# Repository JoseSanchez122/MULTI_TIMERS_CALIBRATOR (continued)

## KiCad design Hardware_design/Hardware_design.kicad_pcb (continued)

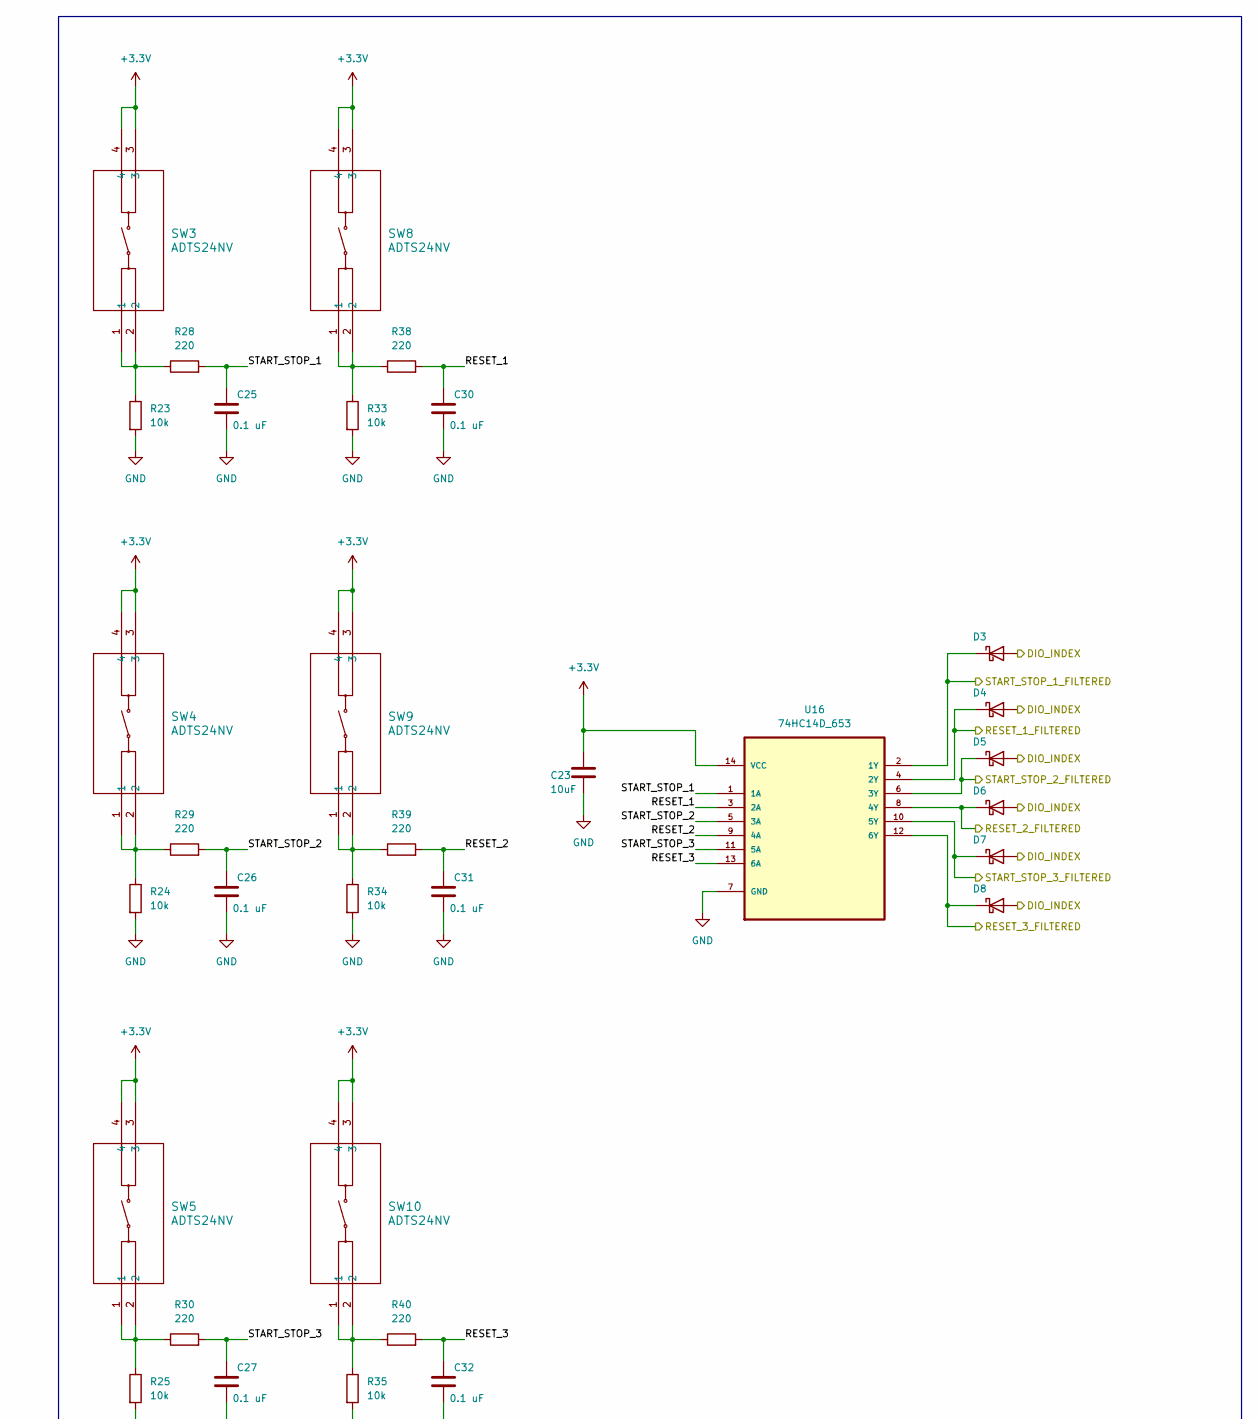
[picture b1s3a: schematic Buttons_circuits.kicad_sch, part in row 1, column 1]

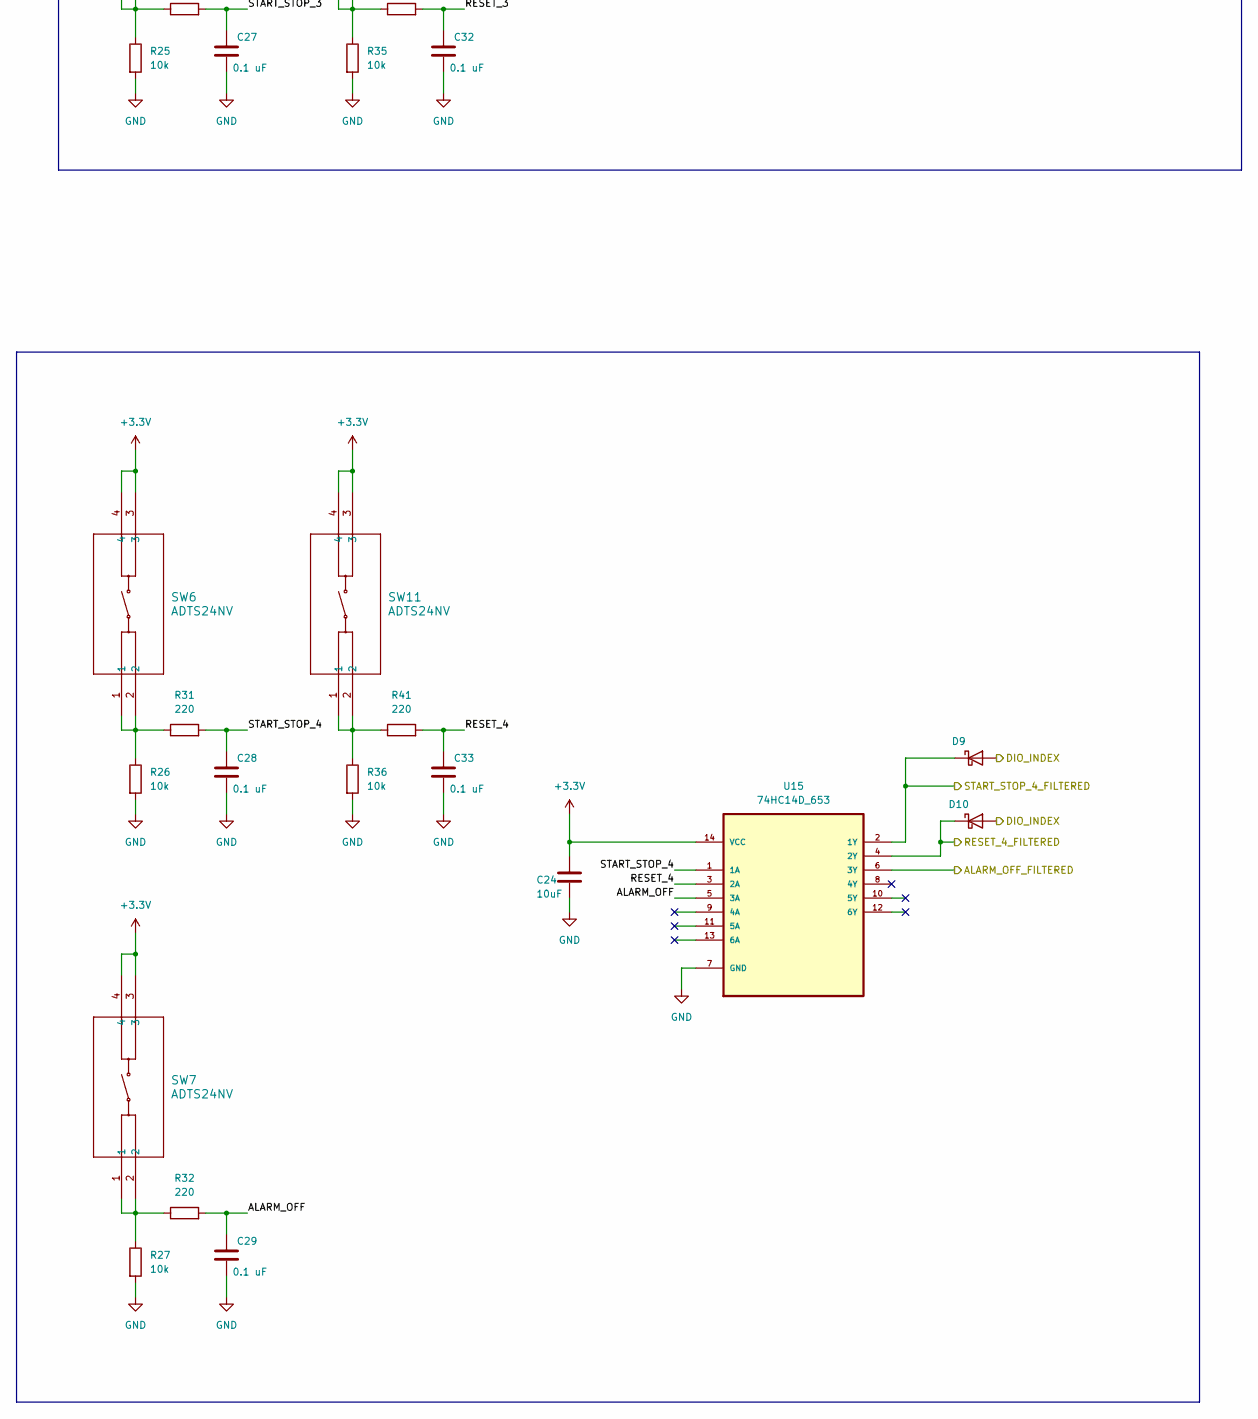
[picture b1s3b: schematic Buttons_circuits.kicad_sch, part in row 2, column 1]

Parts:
C23, C24: 10uF; 0805_SMD_TANT_CAP_T491B106K016AT
C25, C26, C27, C28, C29, C30, C31, C32, C33: 0.1 uF; 0805_SMD_CERAMIC_CAP_T491B106K016AT
D3, D4, D5, D6, D7, D8, D9, D10: D_Schottky; DIO_Schottky _MBR0530T3G
R23, R24, R25, R26, R27, R33, R34, R35, R36: 10k; 0805_RES_RESC2012X60N
R28, R29, R30, R31, R32, R38, R39, R40, R41: 220; 0805_RES_RESC2012X60N
SW3, SW4, SW5, SW6, SW7, SW8, SW9, SW10, SW11: ADTS24NV; PUSH_BUTTON_ADTS24NV
U15, U16: 74HC14D_653; Schimitt_Trigger_74HC14D_653; MPN 74HCT14D,653

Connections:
+3.3V: C23.1, C24.1, SW3.3, SW3.4, SW4.3, SW4.4, SW5.3, SW5.4, SW6.3, SW6.4, SW7.3, SW7.4, SW8.3, SW8.4, SW9.3, SW9.4, SW10.3, SW10.4, SW11.3, SW11.4, U15.14 (VCC), U16.14 (VCC); also elsewhere on the board
/Alarm_OFF_FILTERED: U15.6 (3Y); also elsewhere on the board
/Buttons_circuits/ALARM_OFF: C29.1, R32.2, U15.5 (3A)
/Buttons_circuits/RESET_1: C30.1, R38.2, U16.3 (2A)
/Buttons_circuits/RESET_2: C31.1, R39.2, U16.9 (4A)
/Buttons_circuits/RESET_3: C32.1, R40.2, U16.13 (6A)
/Buttons_circuits/RESET_4: C33.1, R41.2, U15.3 (2A)
/Buttons_circuits/START_STOP_1: C25.1, R28.2, U16.1 (1A)
/Buttons_circuits/START_STOP_2: C26.1, R29.2, U16.5 (3A)
/Buttons_circuits/START_STOP_3: C27.1, R30.2, U16.11 (5A)
/Buttons_circuits/START_STOP_4: C28.1, R31.2, U15.1 (1A)
/INDEX: D3.A, D4.A, D5.A, D6.A, D7.A, D8.A, D9.A, D10.A; also elsewhere on the board
/RESET_1_FILTERED: D4.C (K), U16.4 (2Y); also elsewhere on the board
/RESET_2_FILTERED: D6.C (K), U16.8 (4Y); also elsewhere on the board
/RESET_3_FILTERED: D8.C (K), U16.12 (6Y); also elsewhere on the board
/RESET_4_FILTERED: D10.C (K), U15.4 (2Y); also elsewhere on the board
/START_STOP_1_FILTERED: D3.C (K), U16.2 (1Y); also elsewhere on the board
/START_STOP_2_FILTERED: D5.C (K), U16.6 (3Y); also elsewhere on the board
/START_STOP_3_FILTERED: D7.C (K), U16.10 (5Y); also elsewhere on the board
/START_STOP_4_FILTERED: D9.C (K), U15.2 (1Y); also elsewhere on the board
GND: C23.2, C24.2, C25.2, C26.2, C27.2, C28.2, C29.2, C30.2, C31.2, C32.2, C33.2, R23.2, R24.2, R25.2, R26.2, R27.2, R33.2, R34.2, R35.2, R36.2, U15.7 (GND), U16.7 (GND); also elsewhere on the board
unnamed: R23.1, R28.1, SW3.1, SW3.2
unnamed: R24.1, R29.1, SW4.1, SW4.2
unnamed: R25.1, R30.1, SW5.1, SW5.2
unnamed: R26.1, R31.1, SW6.1, SW6.2
unnamed: R27.1, R32.1, SW7.1, SW7.2
unnamed: R33.1, R38.1, SW8.1, SW8.2
unnamed: R34.1, R39.1, SW9.1, SW9.2
unnamed: R35.1, R40.1, SW10.1, SW10.2
unnamed: R36.1, R41.1, SW11.1, SW11.2

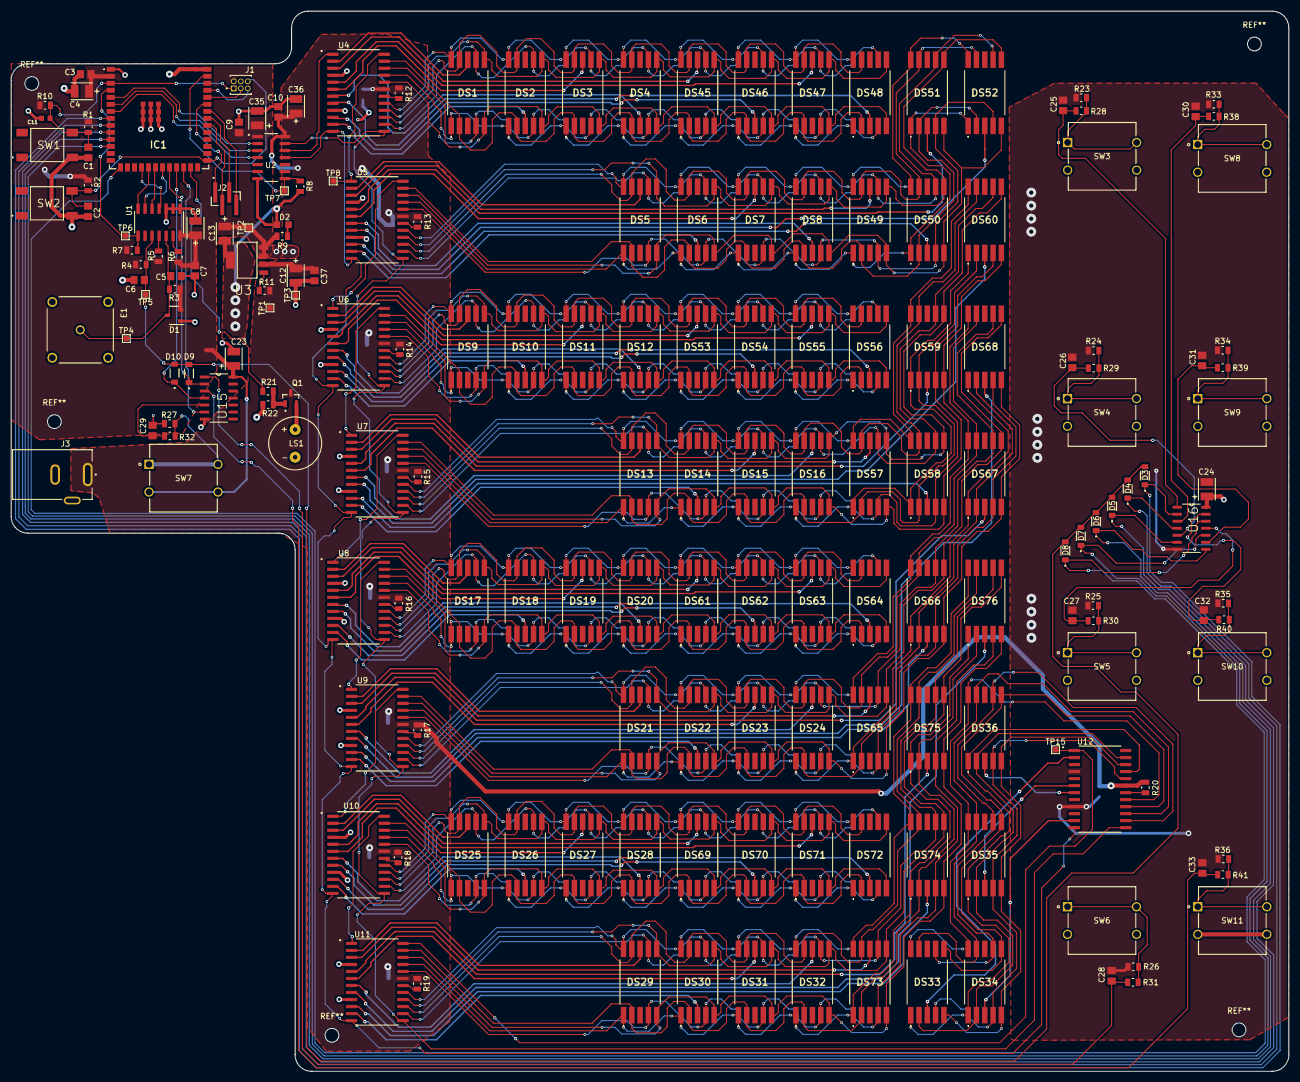
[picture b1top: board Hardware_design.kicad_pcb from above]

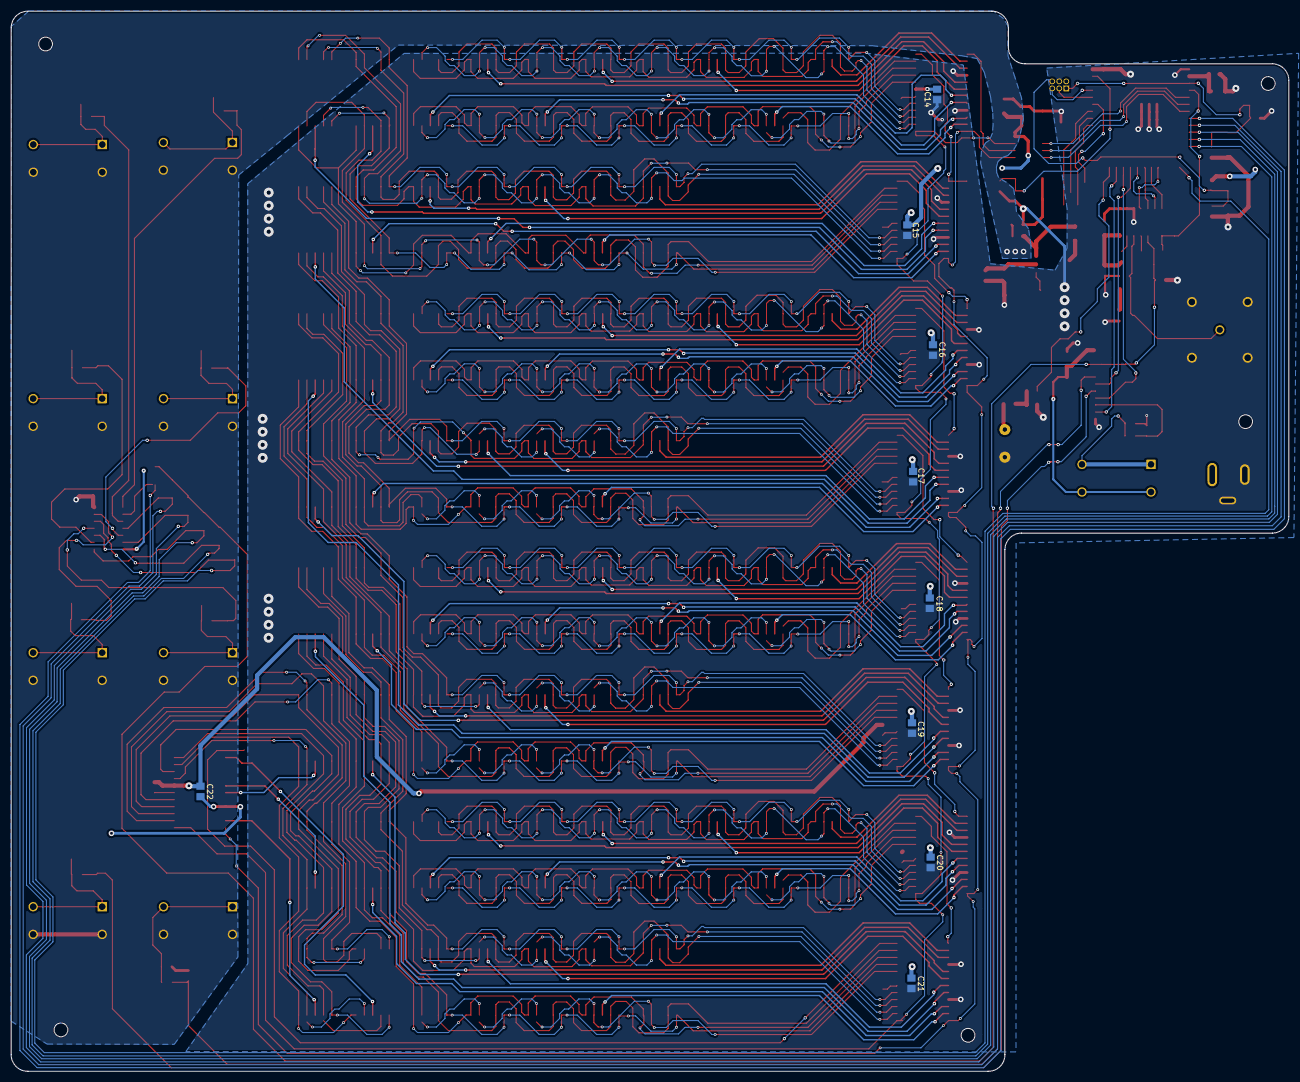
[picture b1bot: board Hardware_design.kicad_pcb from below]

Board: 2 copper layers, 231.3 x 191.9 mm, 195 parts (9 on the bottom side), 216 nets.

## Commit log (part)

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2026-05-24 primeros archivos
    primeros archivos
2026-05-24 sub folder created for examples
2026-05-25 starting the spi comunication example
2026-05-25 starting spi driver configuration
2026-05-29 hardware design initiated
2026-05-29 SPI_comnunication done, starting main firmware
2026-05-29 Update main.c
    seting CNTR to 0 before counting
2026-05-29 first library update
    library in construction, is not finished yet
2026-05-29 init_ls7366r_spi_com function working
2026-05-29 LS7366R library update
    all functions have been moved to the LS7366R library and all of them are working fine. we still need to update the write comand and data function for the endianess bytes
2026-05-30 starting hardware proyect
    looking for componets, symbols, footprints, etc
2026-05-31 starting to add the components
    some symbols and footprints have been added after carefull consideration, there are still more to add
2026-06-02 displays datasheets added
2026-06-05 component_search_finidhed
    starting to design schematics
2026-06-06 INDEX INTERRUPTION working
    the device has been configured for transfering the cntr reg count data to the otr reg so it stores data at a precise moment so when we want to read it later with the esp32se we get the count at that 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
2026-06-06 ISR ATTEMPT
    FOR now isr is not working properly, message is being sent twice, but i'll work on it, don't worry
2026-06-07 interrupt routine working
    the interrupt routine is already working but it is being activated in falling and rising edge, Even though the isr copnfiguration is set to be activaded on falling edge, the problem is that the activ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
2026-06-07 interrupt execution
    interrupt already working, comming from counter flag to esp32 interrupt pin, interruption is being handled properly by esp32 and working fine with the LFLAG interrption flag pin from the counter, it 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
2026-06-08 schematic progress
    saving schematic progress, butons added but a change is pending to use 10 buttons instead of 15
2026-06-08 Buttons number modified
    now the buttons are 10, one is for starting and stoping the count and another one for reseting it
2026-06-08 STARTING THE DISPLAY design
    acording to calculations we will need around 1.848 A when working with all the displays at the same time, including the MAX7221, the 1.848 A consumption is only for the display part.
2026-06-09 display set up completed
    for the displays we will not need an aditional voltage regulator becuase we will use the direct conection from the 5V power supply of the circuit, it needs to be able to provide at least 3A, recomend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
2026-06-11 starting footprint asignment
2026-06-11 all footprints asigned
2026-06-13 pcb layout started
    concecting first MAX7221 and its 8 displays
2026-06-13 10 uF display caps deleted
    10 uF display caps ocupy too much space, they were deleted
2026-06-14 component placement started
    index pin and gpio pins for 10 buttons problem, index pin should be activated whenever any of the 10 buttons is pressed but only the gpio pin of the button that was pressed should also be activaded
2026-06-15 Index problem solved and some progress made
2026-06-21 big update
    coper zones already set, edgecuts set, all components placed, we are just missing the routing
2026-06-21 a little advance
2026-06-28 almost finished
    just missing final conections and verification of constrains for fabrication
